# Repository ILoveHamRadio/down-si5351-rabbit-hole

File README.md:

# down-si5351-rabbit-hole
worksheets, source code, schematics and other great stuff for the "Down the SI5351 Rabbit Hole" build series

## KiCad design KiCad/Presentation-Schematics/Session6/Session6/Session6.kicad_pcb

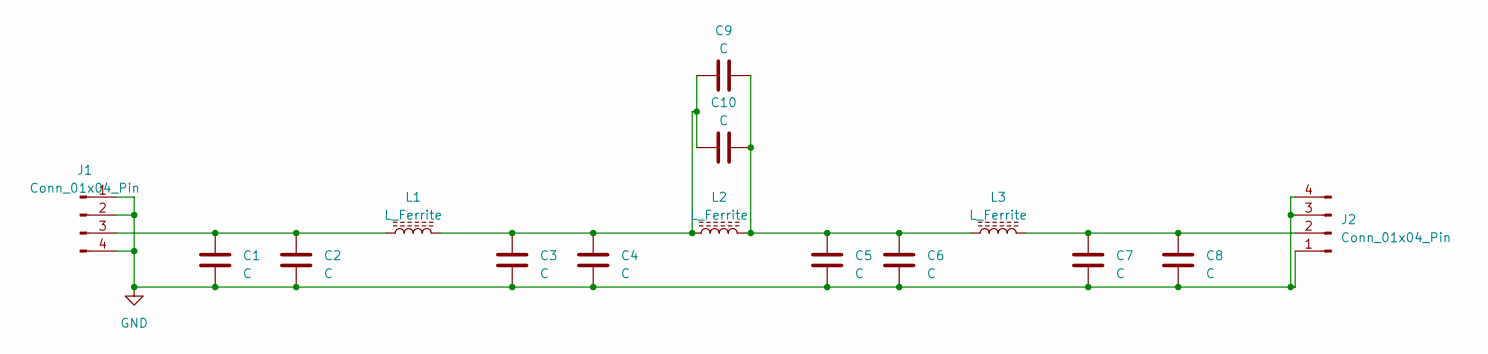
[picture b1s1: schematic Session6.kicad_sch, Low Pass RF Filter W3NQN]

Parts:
C1, C2, C3, C4, C5, C6, C7, C8, C9, C10: C; C_1206_3216Metric_Pad1.33x1.80mm_HandSolder
J1, J2: Conn_01x04_Pin; PinHeader_1x04_P2.54mm_Vertical
L1, L2, L3: L_Ferrite; L_Axial_L5.3mm_D2.2mm_P7.62mm_Horizontal_Vishay_IM-1

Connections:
GND: C1.2, C2.2, C3.2, C4.2, C5.2, C6.2, C7.2, C8.2, J1.1, J1.2, J1.4, J2.1, J2.3, J2.4
unnamed: C3.1, C4.1, C9.1, C10.1, L1.2, L2.1
unnamed: C5.1, C6.1, C9.2, C10.2, L2.2, L3.1
unnamed: C1.1, C2.1, J1.3, L1.1
unnamed: C7.1, C8.1, J2.2, L3.2

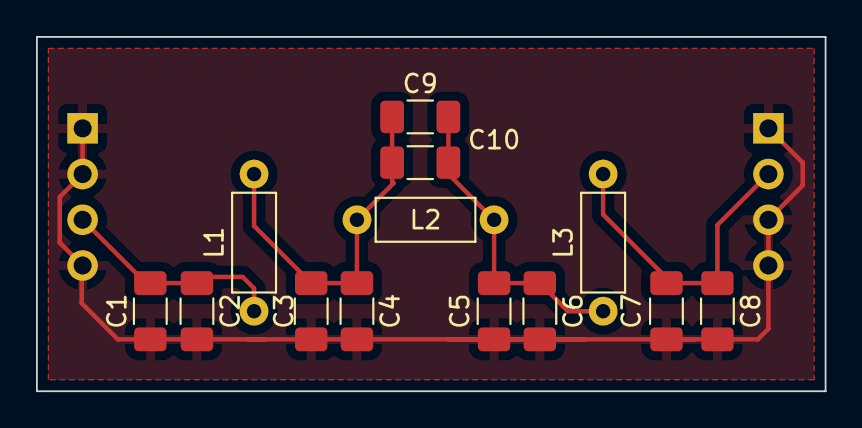
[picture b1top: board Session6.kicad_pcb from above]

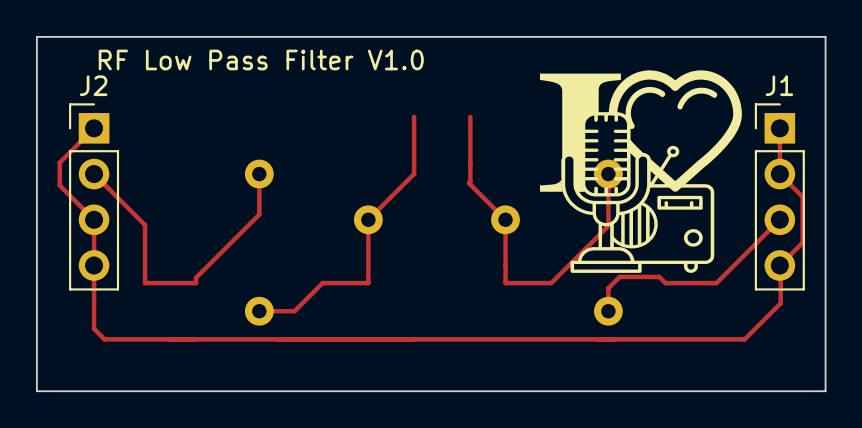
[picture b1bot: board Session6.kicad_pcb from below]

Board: 2 copper layers, 43.8 x 19.7 mm, 15 parts (2 on the bottom side), 5 nets.

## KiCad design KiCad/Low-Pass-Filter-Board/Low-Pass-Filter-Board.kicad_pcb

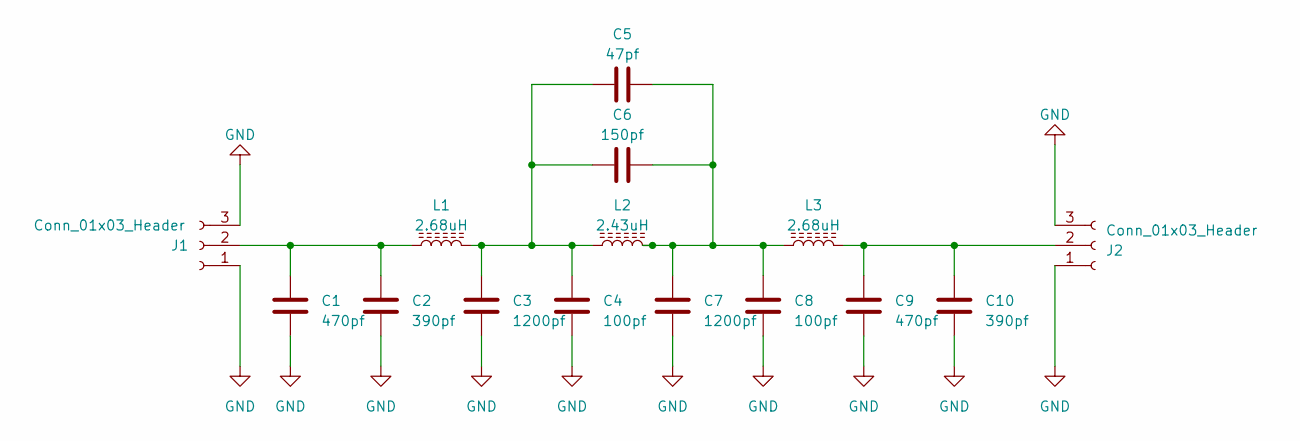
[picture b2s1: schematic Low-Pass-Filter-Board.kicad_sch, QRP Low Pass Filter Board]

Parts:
C1, C9: 470pf; C_1206_3216Metric_Pad1.33x1.80mm_HandSolder
C2, C10: 390pf; C_1206_3216Metric_Pad1.33x1.80mm_HandSolder
C3, C7: 1200pf; C_1206_3216Metric_Pad1.33x1.80mm_HandSolder
C4, C8: 100pf; C_1206_3216Metric_Pad1.33x1.80mm_HandSolder
C5: 47pf; C_1206_3216Metric_Pad1.33x1.80mm_HandSolder
C6: 150pf; C_1206_3216Metric_Pad1.33x1.80mm_HandSolder
J1, J2: Conn_01x03_Header; PinHeader_1x03_P1.00mm_Vertical
L1, L3: 2.68uH; L_Axial_L5.3mm_D2.2mm_P2.54mm_Vertical_Vishay_IM-1
L2: 2.43uH; L_Axial_L5.3mm_D2.2mm_P2.54mm_Vertical_Vishay_IM-1

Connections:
GND: C1.2, C2.2, C3.2, C4.2, C7.2, C8.2, C9.2, C10.2, J1.1, J1.3, J2.1, J2.3
unnamed: C3.1, C4.1, C5.1, C6.1, L1.2, L2.1
unnamed: C5.2, C6.2, C7.1, C8.1, L2.2, L3.1
unnamed: C1.1, C2.1, J1.2, L1.1
unnamed: C9.1, C10.1, J2.2, L3.2

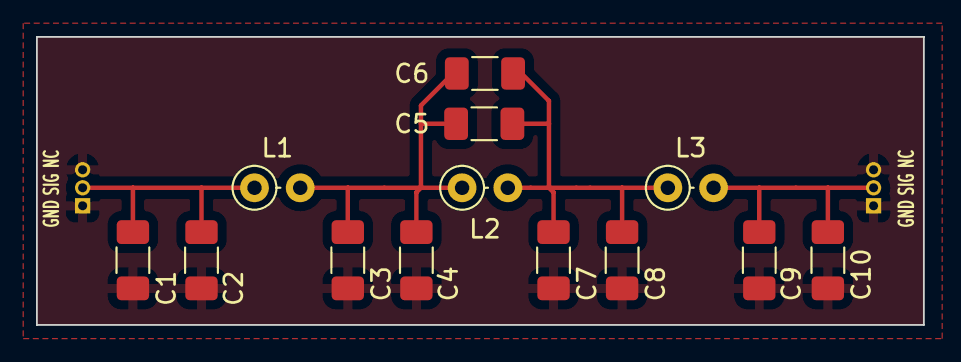
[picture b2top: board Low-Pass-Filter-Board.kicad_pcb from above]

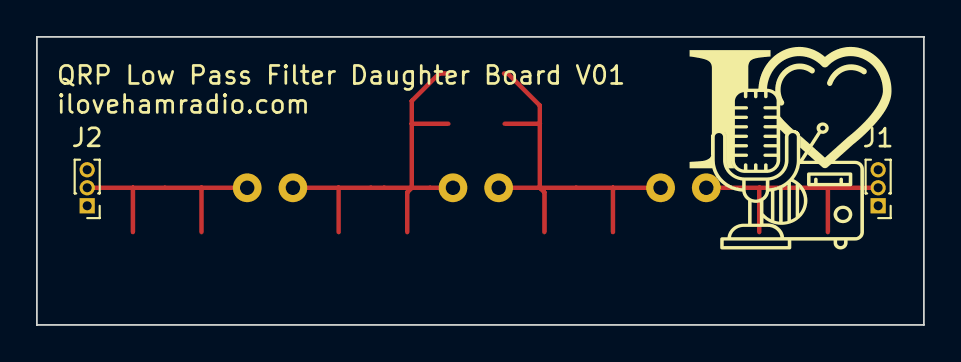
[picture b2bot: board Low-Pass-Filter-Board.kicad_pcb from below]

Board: 2 copper layers, 49.3 x 16.0 mm, 15 parts (2 on the bottom side), 5 nets.

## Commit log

2023-06-27 live code changes during session
2023-06-28 Add start of VFO Display code
2023-06-28 Update serial settings
2023-06-28 Rotary Encoder Basic Sample
2023-06-28 turn off cmake configuration
2023-06-28 VFO Encoder Example Project
2023-06-29 updates from session
2023-07-09 revert code to pre presentation
2023-07-13 updates for session 4
2023-07-13 format file
2023-07-13 updated to tune in 1Khz steps
2023-07-15 Fix upper band limits
2023-07-15 Add 6m to band list
2023-07-15 6m fixes
2023-08-16 session 6 updates
2023-08-16 initial code for cw beacon
2023-08-16 working version
2023-08-17 updated si5351 calibration
2023-08-23 initial code for session 10
2023-08-23 fix build issue
2023-08-23 revert wifi info
2023-08-23 initial code for project
2023-08-23 added code to get formatted date from epoch time
2023-08-24 changes based on session
2023-09-06 Initial Code Example
2023-09-06 add code to calc maidenhead grid
2023-09-06 clean up code
2023-09-06 updated schematic
2023-09-06 initial code
2023-09-06 fixed gps init functions and display issues
2023-09-06 correct misspellings
2023-09-06 add init message on power up
2023-09-07 move schematics up a folder
2023-09-07 Update README.md
    added some more info
2023-09-13 initial WSPR Code
2023-09-14 updates for display
2023-09-16 update schematic to include low pass filter

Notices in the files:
KiCad/Low-Pass-Filter-Board/Low-Pass-Filter-Board.kicad_pcb:
CC by 4.0
KiCad/Low-Pass-Filter-Board/Low-Pass-Filter-Board.kicad_sch:
creativecommons.org/licenses/by/4.0
